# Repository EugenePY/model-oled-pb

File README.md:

# OLED-UTIL

graphic-converter uitls for **ModelOLED**.

## Installation

```zsh
pip install ./ 
```

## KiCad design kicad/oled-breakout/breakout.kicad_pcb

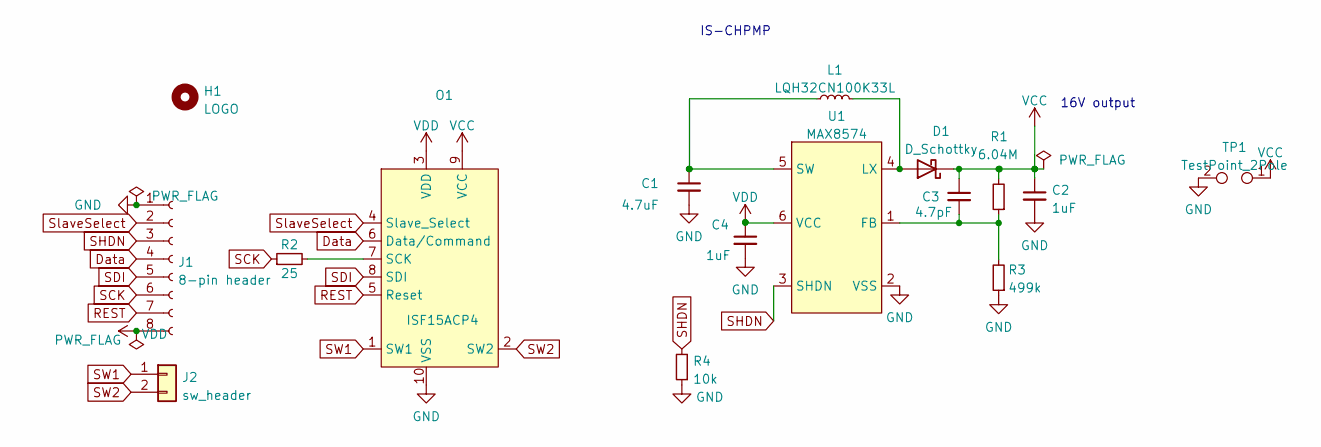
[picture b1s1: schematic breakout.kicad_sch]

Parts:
C1: 4.7uF; C_0603_1608Metric; PART_ID 0603X475M6R3CT
C2, C4: 1uF; C_0603_1608Metric; PART_ID CS1608X7R105K250NRB
C3: 4.7pF; C_0603_1608Metric; PART_ID 0603CG4R7C500NT
D1: D_Schottky; D_SOD-323; PART_ID BAT43WS_R1_00001
H1: LOGO; icon-temp
J1: 8-pin header; PinHeader_1x08_P1.27mm_Vertical
J2: sw_header; PinHeader_1x02_P1.27mm_Vertical
L1: LQH32CN100K33L; L_1210_3225Metric; PART_ID LQH32CN100K33
O1: ISF15ACP4; AT9704-085L; PART_ID ISF15ACP4
R1: 6.04M; R_0805_2012Metric; PART_ID RC0805FR-076M04L
R2: 25; R_0805_2012Metric; PART_ID ARG05BTC0250N
R3: 499k; R_0805_2012Metric; PART_ID ARG05BTC4993
R4: 10k; R_0603_1608Metric; PART_ID RC0603JR-0710KL
TP1: TestPoint_2Pole; TestPoint_2Pads_Pitch2.54mm_Drill0.8mm
U1: MAX8574; SOT-23-6; PART_ID MAX8574EUT+T

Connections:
Data: J1.4, O1.6 (Data/Command)
GND: C1.2, C2.2, C4.2, J1.1, O1.10 (VSS), R3.1, R4.1, TP1.2, U1.2 (VSS)
unnamed: C1.1, L1.1, U1.5 (SW)
unnamed: C3.2, R1.1, R3.2, U1.1 (FB)
unnamed: D1.2 (A), L1.2, U1.4 (LX)
unnamed: O1.7 (SCK), R2.2
REST: J1.7, O1.5 (Reset)
SCK: J1.6, R2.1
SDI: J1.5, O1.8 (SDI)
SHDN: J1.3, R4.2, U1.3 (SHDN)
SW1: J2.1, O1.1 (SW1)
SW2: J2.2, O1.2 (SW2)
SlaveSelect: J1.2, O1.4 (Slave_Select)
VCC: C2.1, C3.1, D1.1 (K), O1.9 (VCC), R1.2, TP1.1
VDD: C4.1, J1.8, O1.3 (VDD), U1.6 (VCC)

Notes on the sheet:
IS-CHPMP
16V output

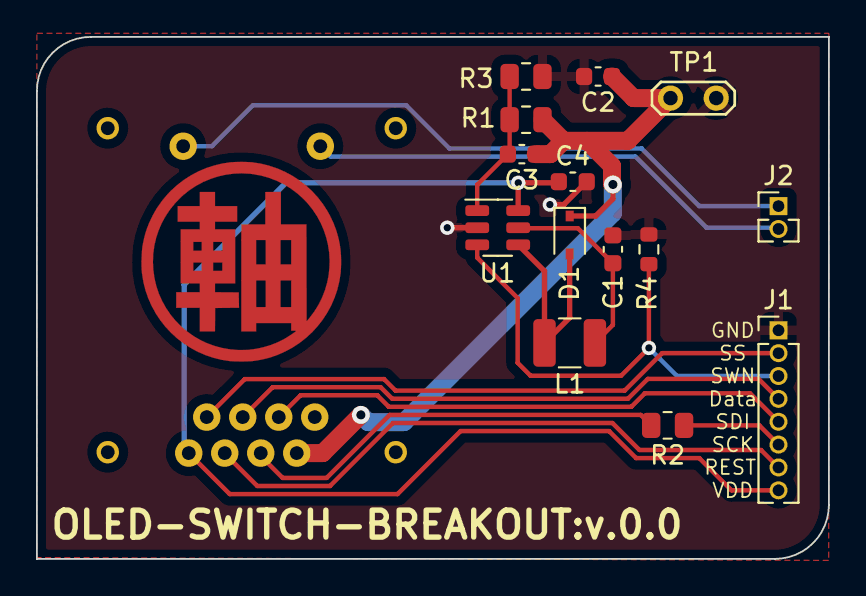
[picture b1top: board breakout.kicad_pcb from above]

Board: 2 copper layers, 44.0 x 29.0 mm, 16 parts (0 on the bottom side), 15 nets.

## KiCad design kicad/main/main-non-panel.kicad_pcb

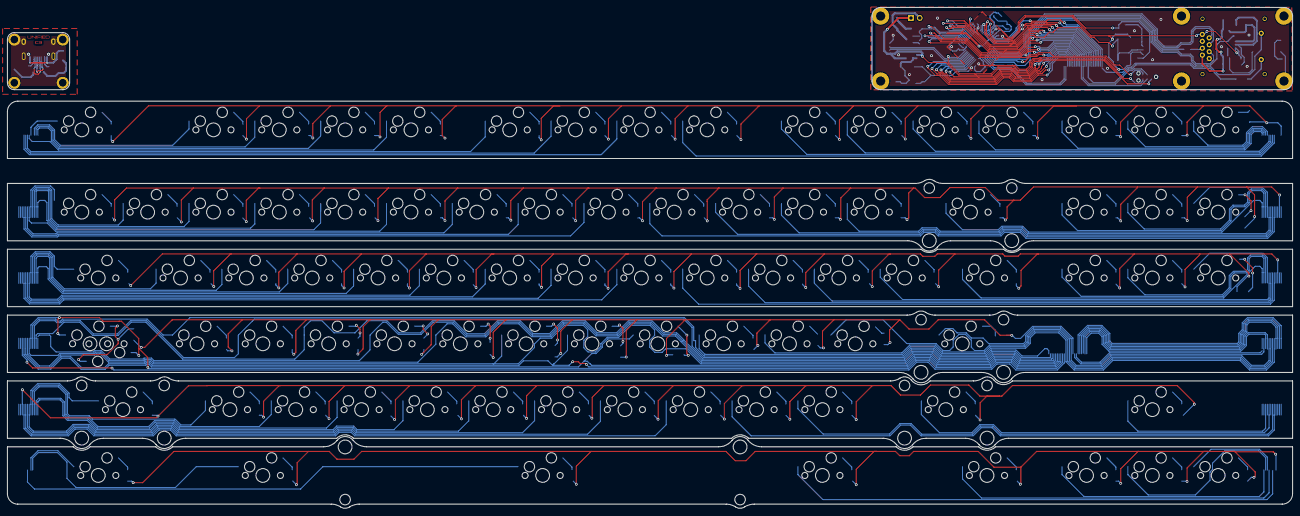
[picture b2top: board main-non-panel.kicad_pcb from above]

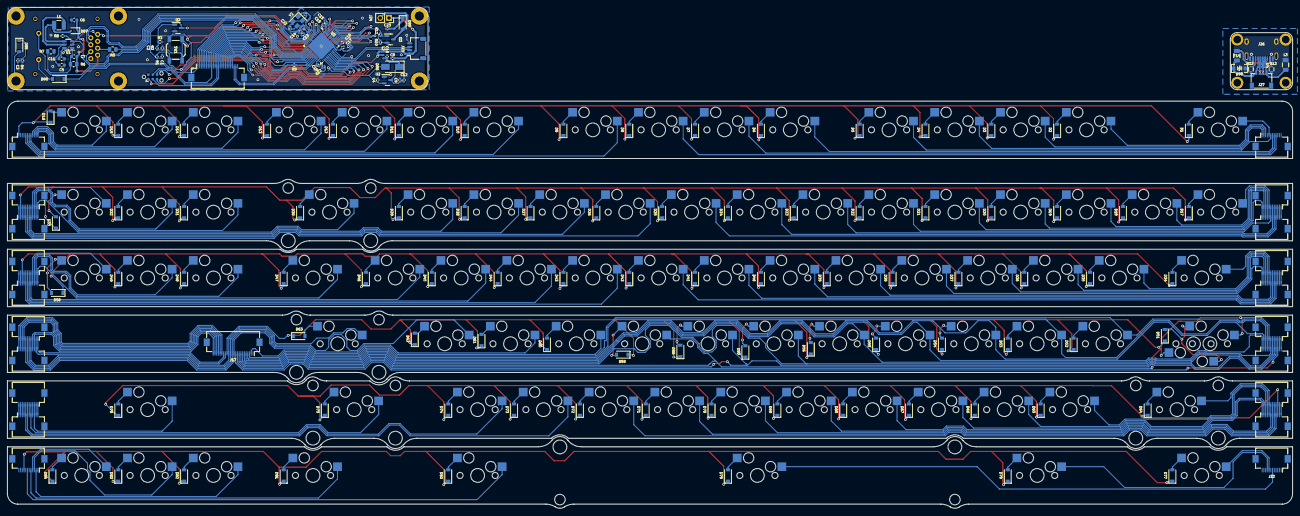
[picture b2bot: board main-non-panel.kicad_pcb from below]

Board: 2 copper layers, 371.9 x 144.9 mm, 263 parts (169 on the bottom side), 144 nets.

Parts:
!1: MX-NoLED; MXOnly-1U-Hotswap
$1: MX-NoLED; MXOnly-1U-Hotswap
%1: MX-NoLED; MXOnly-1U-Hotswap
&1: MX-NoLED; MXOnly-1U-Hotswap
''1: MX-NoLED; MXOnly-1U-Hotswap
(1: MX-NoLED; MXOnly-1U-Hotswap
)1: MX-NoLED; MXOnly-1U-Hotswap
*1: MX-NoLED; MXOnly-1U-Hotswap
+1: MX-NoLED; MXOnly-1U-Hotswap
:1: MX-NoLED; MXOnly-1U-Hotswap
<1: MX-NoLED; MXOnly-1U-Hotswap
>1: MX-NoLED; MXOnly-1U-Hotswap
@1: MX-NoLED; MXOnly-1U-Hotswap
A1: MX-NoLED; MXOnly-1U-Hotswap
B1: MX-NoLED; MXOnly-1U-Hotswap
BS1: MX-NoLED; MXOnly-2U-Hotswap
C1: 470nF; C_0402_1005Metric
C2, C3, C20, C23: 4.7uF; C_0402_1005Metric
C4, C12, C14: 1uF; C_0402_1005Metric
C5: 4.7uF; C_0603_1608Metric
C6, C11: 1uF; C_0603_1608Metric
C7: 4.7pF; C_0603_1608Metric
C8, C13: 10nF; C_0402_1005Metric
C9, C15, C16, C17, C18, C19: 100nF; C_0402_1005Metric
C10: 4.7nF; C_0402_1005Metric
C21, C22: 30pF; C_0402_1005Metric
CAP1: MX-NoLED; MXOnly-1.75U-Hotswap
CAP2: Steped-Cap; MXOnly-1.25U-Hotswap
D1, D2, D3, D4, D5, D6, D7, D8, D9, D10, D11, D12, D13, D14, D15, D16, D17, D18, D19, D20, D21, D22, D23, D24, D25, D26, D27, D28, D29, D30, D31, D32, D33, D34, D35, D36, D37, D38, D39, D40, D41, D42, D43, D44, D45, D46, D47, D48, D49, D50, D51, D52, D53, D54, D55, D56, D57, D58, D59, D60, D61, D62, D63, D64, D65, D66, D67, D68, D69, D70, D71, D72, D73, D74, D75, D76, D77, D78, D79, D80, D81, D82, D83, D84, D85, D88: 1N4148W; D_SOD-123
D86: SS34; D_SMA
D87: D_Schottky; D_SOD-323
D89: freewheeling diode; D_SOD-123
D90: SMF9.0CA; D_SOD-123_Bidirectional
Delete1: MX-NoLED; MXOnly-1U-Hotswap
Down1: MX-NoLED; MXOnly-1U-Hotswap
E1: MX-NoLED; MXOnly-1U-Hotswap
End1: MX-NoLED; MXOnly-1U-Hotswap
Enter1: MX-NoLED; MXOnly-2.25U-Hotswap
Esc1: MX-NoLED; MXOnly-1U-Hotswap
F1, F2, F3, F4, F5, F6, F7, F8, F9, F10, F11, F12, F13: MX-NoLED; MXOnly-1U-Hotswap
F14: ASMD1206-150; Fuse_1206_3216Metric
G1: MX-NoLED; MXOnly-1U-Hotswap
G2: name; Unified-Daughterboard-Name.pretty
G3: logo; Unified-Daughterboard-Logo.pretty
H1: MX-NoLED; MXOnly-1U-Hotswap
H2, H3, H4, H5, H6, H7: M2.5; MountingHole_2.7mm_M2.5_Pad
Home1: MX-NoLED; MXOnly-1U-Hotswap
I1: MX-NoLED; MXOnly-1U-Hotswap
Insert1: MX-NoLED; MXOnly-1U-Hotswap
J1, J3, J5, J7, J9, J11, J13, J15, J19, J21: Conn_01x12_Male; Hirose_FH12-12S-0.5SH_1x12-1MP_P0.50mm_Horizontal
J2, J4, J6, J8, J10, J12, J14, J18, J20, J22: Conn_01x12_Female; Hirose_FH12-12S-0.5SH_1x12-1MP_P0.50mm_Horizontal
J16, J17: switch_board; Hirose_FH12-24S-0.5SH_1x24-1MP_P0.50mm_Horizontal
J23: JST-4 pins; JST_SH_SM04B-SRSS-TB_1x04-1MP_P1.00mm_Horizontal
J24: solenoid; PinSocket_1x02_P2.54mm_Vertical
J25: SWD/JTAG-4pin; Tag-Connect_TC2030-IDC-NL_2x03_P1.27mm_Vertical
J26: TYPE-C-31-M12_13; TYPE-C-31-M-12
J27: JST-4 pins; JST-SR-4
K1: MX-NoLED; MXOnly-1U-Hotswap
L1: LQH32CN100K33L; L_1210_3225Metric
L2: 33R@100MH; L_0402_1005Metric
L3: 60R@100MHz; L_1206_3216Metric
LAlt1: MX-NoLED; MXOnly-1.5U-Hotswap
LCtrl1: MX-NoLED; MXOnly-1.5U-Hotswap
LShift1: MX-NoLED; MXOnly-2.25U-Hotswap
Left1: MX-NoLED; MXOnly-1U-Hotswap
M1: MX-NoLED; MXOnly-1U-Hotswap
MH1, MH2, MH4: Mount-M2; Generic-Mounthole
MH3: mouting-hole; Generic-Mounthole
MX_C1: MX-NoLED; MXOnly-1U-Hotswap
MX_D1: MX-NoLED; MXOnly-1U-Hotswap
MX_J1: MX-NoLED; MXOnly-1U-Hotswap
MX_L1: MX-NoLED; MXOnly-1U-Hotswap
MX_R1: MX-NoLED; MXOnly-1U-Hotswap
MX_U1: MX-NoLED; MXOnly-1U-Hotswap
N1: MX-NoLED; MXOnly-1U-Hotswap
O1: MX-NoLED; MXOnly-1U-Hotswap
O2: ISF15ACP4; AT9704-085L
P1: MX-NoLED; MXOnly-1U-Hotswap
PB1: MX-NoLED; MXOnly-1U-Hotswap
PgDn1: MX-NoLED; MXOnly-1U-Hotswap
PgUp1: MX-NoLED; MXOnly-1U-Hotswap
PrtSc1: MX-NoLED; MXOnly-1U-Hotswap
Q1: MX-NoLED; MXOnly-1U-Hotswap
Q2: 2N7002; SOT-23
Q3: SI2302; SOT-23
R1, R2, R8, R9, R10: 10k; R_0402_1005Metric
R3: 100k; R_0402_1005Metric
R4: 1M; R_0402_1005Metric
R5: 25; R_0805_2012Metric
R6: 6.04M; R_0805_2012Metric
R7: 499k; R_0805_2012Metric
R11: 1k; R_0402_1005Metric
R12, R13: 5.1k; R_0603
RAlt1: MX-NoLED; MXOnly-1.5U-Hotswap
RCtrl1: MX-NoLED; MXOnly-1.5U-Hotswap
RShift1: MX-NoLED; MXOnly-2.75U-Hotswap
Right1: MX-NoLED; MXOnly-1U-Hotswap
S1: MX-NoLED; MXOnly-1U-Hotswap
SL1: MX-NoLED; MXOnly-1U-Hotswap
SW1: SW_Push; SW_SPST_SKQG_WithoutStem
Spc1: MX-NoLED; MXOnly-7U-Hotswap-ReversedStabilizers
T1: MX-NoLED; MXOnly-1U-Hotswap
TAB1: MX-NoLED; MXOnly-1.5U-Hotswap
U1: MAX8574; SOT-23-6
U2: MCP1754S-3302xCB; SOT-23
U3: STM32F103CBUx; QFN-48-1EP_7x7mm_P0.5mm_EP5.6x5.6mm
U4: TPD4E05U06DQAR; USON-10_2.5x1.0mm_P0.5mm
Up1: MX-NoLED; MXOnly-1U-Hotswap
V1: MX-NoLED; MXOnly-1U-Hotswap
W1: MX-NoLED; MXOnly-1U-Hotswap
X1: MX-NoLED; MXOnly-1U-Hotswap
Y1: MX-NoLED; MXOnly-1U-Hotswap
Y2: 8MHz; Crystal_SMD_3225-4Pin_3.2x2.5mm
Z1: MX-NoLED; MXOnly-1U-Hotswap
\1: MX-NoLED; MXOnly-1U-Hotswap
\#1: MX-NoLED; MXOnly-1U-Hotswap
\QM1: MX-NoLED; MXOnly-1U-Hotswap
^1: MX-NoLED; MXOnly-1U-Hotswap
_1: MX-NoLED; MXOnly-1U-Hotswap
{1: MX-NoLED; MXOnly-1U-Hotswap
|1: MX-NoLED; MXOnly-1.5U-Hotswap
}1: MX-NoLED; MXOnly-1U-Hotswap

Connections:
+5V: C9.1, C10.1, C12.1, D86.1 (K), L2.2, U2.3 (VI)
BOOT0: C2.1, R2.2, SW1.1, U3.44 (BOOT0)
BOOT1: R9.1, U3.20 (PB2)
D+: J23.3, U3.33 (PA12)
D-: J23.2, U3.32 (PA11)
DA+: J26.A6 (D+), J26.B6 (D+), J27.3, U4.1 (IO1), U4.4 (D2+), U4.7 (NC), U4.10 (NC)
DA-: J26.A7 (D-), J26.B7 (D-), J27.2, U4.2 (IO2), U4.5 (D2-), U4.6 (NC), U4.9 (NC)
Data: O2.6 (Data/Command), U3.13 (PA3)
GND: C1.2, C3.2, C4.2, C5.2, C6.2, C8.2, C9.2, C10.2, C11.2, C12.2, C13.2, C14.2, C15.2, C16.2, C17.2, C18.2, C19.2, C20.2, C21.2, C22.1, C23.2, J23.4, J25.2, J27.4, L3.1, O2.10 (VSS), Q2.2 (S), Q3.2 (S), R2.1, R3.2, R4.2, R7.1, R8.1, R9.2, R10.1, U1.2 (VSS), U2.1 (GND), U3.8 (VSSA), U3.23 (VSS), U3.35 (VSS), U3.47 (VSS), U3.49 (VSS), Y2.2, Y2.4
GNDPWR: D90.1 (A1), J26.A1 (GND), J26.B1 (GND), J26.S (SHIELD), L3.2, MH2.1, R12.2, R13.2, U4.3 (GND), U4.8 (GND)
NRST: C1.1, Q2.3 (D), R1.1, U3.7 (NRST)
unnamed: !1.2 (ROW), D18.2 (A)
unnamed: $1.2 (ROW), D21.2 (A)
unnamed: %1.2 (ROW), D22.2 (A)
unnamed: &1.2 (ROW), D24.2 (A)
unnamed: ''1.2 (ROW), D62.2 (A)
unnamed: (1.2 (ROW), D26.2 (A)
unnamed: )1.2 (ROW), D27.2 (A)
unnamed: *1.2 (ROW), D25.2 (A)
unnamed: +1.2 (ROW), D29.2 (A)
unnamed: :1.2 (ROW), D61.2 (A)
unnamed: <1.2 (ROW), D72.2 (A)
unnamed: >1.2 (ROW), D73.2 (A)
unnamed: @1.2 (ROW), D19.2 (A)
unnamed: A1.2 (ROW), D52.2 (A)
unnamed: B1.2 (ROW), D69.2 (A)
unnamed: BS1.2 (ROW), D30.2 (A)
unnamed: C2.2, Q2.1 (G), R3.1
unnamed: C3.1, D85.1 (K), R4.1
unnamed: C5.1, L1.1, U1.5 (SW)
unnamed: C7.2, R6.1, R7.2, U1.1 (FB)
unnamed: CAP1.2 (ROW), CAP2.2 (ROW), D51.2 (A)
unnamed: D1.2 (A), Esc1.2 (ROW)
unnamed: D2.2 (A), F1.2 (ROW)
unnamed: D3.2 (A), F2.2 (ROW)
unnamed: D4.2 (A), F3.2 (ROW)
unnamed: D5.2 (A), F4.2 (ROW)
unnamed: D6.2 (A), F5.2 (ROW)
unnamed: D7.2 (A), F6.2 (ROW)
unnamed: D8.2 (A), F7.2 (ROW)
unnamed: D9.2 (A), F8.2 (ROW)
unnamed: D10.2 (A), F9.2 (ROW)
unnamed: D11.2 (A), F10.2 (ROW)
unnamed: D12.2 (A), F11.2 (ROW)
unnamed: D13.2 (A), F12.2 (ROW)
unnamed: D14.2 (A), PrtSc1.2 (ROW)
unnamed: D15.2 (A), SL1.2 (ROW)
unnamed: D16.2 (A), PB1.2 (ROW)
unnamed: D17.2 (A), \1.2 (ROW)
unnamed: D20.2 (A), \#1.2 (ROW)
unnamed: D23.2 (A), ^1.2 (ROW)
unnamed: D28.2 (A), _1.2 (ROW)
unnamed: D31.2 (A), Insert1.2 (ROW)
unnamed: D32.2 (A), Home1.2 (ROW)
unnamed: D33.2 (A), PgUp1.2 (ROW)
unnamed: D34.2 (A), TAB1.2 (ROW)
unnamed: D35.2 (A), Q1.2 (ROW)
unnamed: D36.2 (A), W1.2 (ROW)
unnamed: D37.2 (A), E1.2 (ROW)
unnamed: D38.2 (A), MX_R1.2 (ROW)
unnamed: D39.2 (A), T1.2 (ROW)
unnamed: D40.2 (A), Y1.2 (ROW)
unnamed: D41.2 (A), MX_U1.2 (ROW)
unnamed: D42.2 (A), I1.2 (ROW)
unnamed: D43.2 (A), O1.2 (ROW)
unnamed: D44.2 (A), P1.2 (ROW)
unnamed: D45.2 (A), {1.2 (ROW)
unnamed: D46.2 (A), }1.2 (ROW)
unnamed: D47.2 (A), |1.2 (ROW)
unnamed: D48.2 (A), Delete1.2 (ROW)
unnamed: D49.2 (A), End1.2 (ROW)
unnamed: D50.2 (A), PgDn1.2 (ROW)
unnamed: D53.2 (A), S1.2 (ROW)
unnamed: D54.2 (A), MX_D1.2 (ROW)
unnamed: D55.2 (A), F13.2 (ROW)
unnamed: D56.2 (A), G1.2 (ROW)
unnamed: D57.2 (A), H1.2 (ROW)
unnamed: D58.2 (A), MX_J1.2 (ROW)
unnamed: D59.2 (A), K1.2 (ROW)
unnamed: D60.2 (A), MX_L1.2 (ROW)
unnamed: D63.2 (A), Enter1.2 (ROW)
unnamed: D64.2 (A), LShift1.2 (ROW)
unnamed: D65.2 (A), Z1.2 (ROW)
unnamed: D66.2 (A), X1.2 (ROW)
unnamed: D67.2 (A), MX_C1.2 (ROW)
unnamed: D68.2 (A), V1.2 (ROW)
unnamed: D70.2 (A), N1.2 (ROW)
unnamed: D71.2 (A), M1.2 (ROW)
unnamed: D74.2 (A), \QM1.2 (ROW)
unnamed: D75.2 (A), RShift1.2 (ROW)
unnamed: D76.2 (A), Up1.2 (ROW)
unnamed: D77.2 (A), LCtrl1.2 (ROW)
unnamed: D78.2 (A), LAlt1.2 (ROW)
unnamed: D79.2 (A), Spc1.2 (ROW)
unnamed: D80.2 (A), RAlt1.2 (ROW)
unnamed: D81.2 (A), RCtrl1.2 (ROW)
unnamed: D82.2 (A), Left1.2 (ROW)
unnamed: D83.2 (A), Down1.2 (ROW)
unnamed: D84.2 (A), Right1.2 (ROW)
unnamed: D85.2 (A), H2.1
unnamed: D87.2 (A), L1.2, U1.4 (LX)
unnamed: J26.A5 (CC1), R12.1
unnamed: J26.B5 (CC2), R13.1
unnamed: O2.7 (SCK), R5.2
unnamed: Q3.1 (G), R11.2
OLED_SHDN: R8.2, U1.3 (SHDN), U3.19 (PB1)
R0C0_1: $1.1 (COL), F3.1 (COL), F13.1 (COL), J1.1, J2.12, J5.1, J6.12, J9.1, J10.12, J15.1, J16.20, J17.5, J18.12, J21.1, J22.12, MX_R1.1 (COL), U3.30 (PA9), V1.1 (COL)
R0C0_2: E1.1 (COL), F2.1 (COL), J1.2, J2.11, J5.2, J6.11, J9.2, J10.11, J15.2, J16.21, J17.4, J18.11, J21.2, J22.11, MX_C1.1 (COL), MX_D1.1 (COL), U3.31 (PA10), \#1.1 (COL)
R0C0_3: @1.1 (COL), F1.1 (COL), J1.3, J2.10, J5.3, J6.10, J9.3, J10.10, J15.3, J16.22, J17.3, J18.10, J21.3, J22.10, S1.1 (COL), U3.22 (PB11), W1.1 (COL), X1.1 (COL)
R0C0_4: !1.1 (COL), A1.1 (COL), J1.4, J2.9, J5.4, J6.9, J9.4, J10.9, J15.4, J16.23, J17.2, J18.9, J21.4, J22.9, LAlt1.1 (COL), Q1.1 (COL), U3.21 (PB10), Z1.1 (COL)
R0C0_5: CAP1.1 (COL), CAP2.1 (COL), Esc1.1 (COL), J1.5, J2.8, J5.5, J6.8, J9.5, J10.8, J15.5, J16.15, J17.10, J18.8, J21.5, J22.8, LCtrl1.1 (COL), LShift1.1 (COL), TAB1.1 (COL), U3.18 (PB0), \1.1 (COL)
R0C0_6: %1.1 (COL), B1.1 (COL), F4.1 (COL), G1.1 (COL), J1.6, J2.7, J5.6, J6.7, J9.6, J10.7, J15.6, J16.19, J17.6, J18.7, J21.6, J22.7, T1.1 (COL), U3.29 (PA8)
R0C0_7: F5.1 (COL), H1.1 (COL), J1.7, J2.6, J5.7, J6.6, J9.7, J10.6, J15.7, J16.18, J17.7, J18.6, J21.7, J22.6, N1.1 (COL), Spc1.1 (COL), U3.28 (PB15), Y1.1 (COL), ^1.1 (COL)
R0C0_8: &1.1 (COL), F6.1 (COL), J1.8, J2.5, J5.8, J6.5, J9.8, J10.5, J15.8, J16.16, J17.9, J18.5, J21.8, J22.5, M1.1 (COL), MX_J1.1 (COL), MX_U1.1 (COL), U3.26 (PB13)
R0C0_9: *1.1 (COL), <1.1 (COL), F7.1 (COL), I1.1 (COL), J1.9, J2.4, J5.9, J6.4, J9.9, J10.4, J15.9, J16.17, J17.8, J18.4, J21.9, J22.4, K1.1 (COL), U3.27 (PB14)
R0C0_10: D64.1 (K), D65.1 (K), D66.1 (K), D67.1 (K), D68.1 (K), D69.1 (K), D70.1 (K), D71.1 (K), D72.1 (K), D73.1 (K), D74.1 (K), D75.1 (K), D76.1 (K), J1.10, J2.3, J5.10, J6.3, J9.10, J10.3, J15.10, J16.14, J17.11, J18.3, J21.10, J22.3, U3.16 (PA6)
R0C0_11: J1.11, J2.2, J5.11, J6.2, J9.11, J10.2, J15.11, J18.2, J21.11, J22.2
R0C0_12: J1.12, J2.1, J5.12, J6.1, J9.12, J10.1, J15.12, J18.1, J21.12, J22.1
R0C1_1: D1.1 (K), D2.1 (K), D3.1 (K), D4.1 (K), D5.1 (K), D6.1 (K), D7.1 (K), D8.1 (K), D9.1 (K), D10.1 (K), D11.1 (K), D12.1 (K), D13.1 (K), D14.1 (K), D15.1 (K), D16.1 (K), J3.1, J4.12, J7.1, J8.12, J11.1, J12.12, J13.1, J14.12, J16.6, J17.19, J19.1, J20.12, U3.2 (PC13)
R0C1_2: D17.1 (K), D18.1 (K), D19.1 (K), D20.1 (K), D21.1 (K), D22.1 (K), D23.1 (K), D24.1 (K), D25.1 (K), D26.1 (K), D27.1 (K), D28.1 (K), D29.1 (K), D30.1 (K), D31.1 (K), D32.1 (K), D33.1 (K), J3.2, J4.11, J7.2, J8.11, J11.2, J12.11, J13.2, J14.11, J16.5, J17.20, J19.2, J20.11, U3.3 (PC14)
R0C1_3: D34.1 (K), D35.1 (K), D36.1 (K), D37.1 (K), D38.1 (K), D39.1 (K), D40.1 (K), D41.1 (K), D42.1 (K), D43.1 (K), D44.1 (K), D45.1 (K), D46.1 (K), D47.1 (K), D48.1 (K), D49.1 (K), D50.1 (K), J3.3, J4.10, J7.3, J8.10, J11.3, J12.10, J13.3, J14.10, J16.4, J17.21, J19.3, J20.10, U3.4 (PC15)
R0C1_4: D77.1 (K), D78.1 (K), D79.1 (K), D80.1 (K), D81.1 (K), D82.1 (K), D83.1 (K), D84.1 (K), J3.4, J4.9, J7.4, J8.9, J11.4, J12.9, J13.4, J14.9, J16.3, J17.22, J19.4, J20.9, U3.12 (PA2)
R0C1_5: (1.1 (COL), >1.1 (COL), F8.1 (COL), J3.5, J4.8, J7.5, J8.8, J11.5, J12.8, J13.5, J14.8, J16.13, J17.12, J19.5, J20.8, J25.3, MX_L1.1 (COL), O1.1 (COL), U3.38 (PA15)
R0C1_6: )1.1 (COL), :1.1 (COL), F9.1 (COL), J3.6, J4.7, J7.6, J8.7, J11.6, J12.7, J13.6, J14.7, J16.12, J17.13, J19.6, J20.7, J25.4, P1.1 (COL), RAlt1.1 (COL), U3.39 (PB3), \QM1.1 (COL)
R0C1_7: ''1.1 (COL), F10.1 (COL), J3.7, J4.6, J7.7, J8.6, J11.7, J12.6, J13.7, J14.6, J16.11, J17.14, J19.7, J20.6, U3.41 (PB5), _1.1 (COL), {1.1 (COL)
R0C1_8: +1.1 (COL), Enter1.1 (COL), F11.1 (COL), J3.8, J4.5, J7.8, J8.5, J11.8, J12.5, J13.8, J14.5, J16.10, J17.15, J19.8, J20.5, RCtrl1.1 (COL), RShift1.1 (COL), U3.42 (PB6), }1.1 (COL)
R0C1_9: J3.9, J4.4, J7.9, J8.4, J11.9, J12.4, J13.9, J14.4, J16.2, J17.23, J19.9, J20.4, PB1.1 (COL), PgDn1.1 (COL), PgUp1.1 (COL), Right1.1 (COL), U3.11 (PA1)
R0C1_10: Down1.1 (COL), End1.1 (COL), Home1.1 (COL), J3.10, J4.3, J7.10, J8.3, J11.10, J12.3, J13.10, J14.3, J16.1, J17.24, J19.10, J20.3, O2.1 (SW1), SL1.1 (COL), U3.10 (PA0), Up1.1 (COL)
R0C1_11: Delete1.1 (COL), Insert1.1 (COL), J3.11, J4.2, J7.11, J8.2, J11.11, J12.2, J13.11, J14.2, J16.8, J17.17, J19.11, J20.2, Left1.1 (COL), PrtSc1.1 (COL), U3.45 (PB8)
R0C1_12: BS1.1 (COL), F12.1 (COL), J3.12, J4.1, J7.12, J8.1, J11.12, J12.1, J13.12, J14.1, J16.7, J17.18, J19.12, J20.1, U3.46 (PB9), |1.1 (COL)
RCC_OSC_IN: C21.1, U3.5 (PD0), Y2.1
RCC_OSC_OUT: C22.2, U3.6 (PD1), Y2.3
SCK: R5.1, U3.15 (PA5)
SDI: O2.8 (SDI), U3.17 (PA7)
SPI1_NSS: O2.4 (Slave_Select), U3.14 (PA4)
SW2: D88.2 (A), O2.2 (SW2)
SYS_SWCLK: J25.6, U3.37 (PA14)
SYS_SWDIO: J25.5, U3.34 (PA13)
Solenoid_Driver: R10.2, R11.1, U3.40 (PB4)
Solenoid_Neg: D89.2 (A), J24.2, Q3.3 (D)
Solenoid_Pos: C8.1, C23.1, D89.1 (K), F14.1, J23.1, J24.1, J25.1, J26.A4 (VBUS), J26.B4 (VBUS), L2.1
VCC: C6.1, C7.1, D87.1 (K), D90.2 (A2), F14.2, J27.1, O2.9 (VCC), R6.2
VDD: C4.1, C11.1, C13.1, C14.1, C15.1, C16.1, C17.1, C18.1, C19.1, C20.1, D86.2 (A), O2.3 (VDD), R1.2, SW1.2, U1.6 (VCC), U2.2 (VO), U3.1 (VBAT), U3.9 (VDDA), U3.24 (VDD), U3.36 (VDD), U3.48 (VDD)
row3: D51.1 (K), D52.1 (K), D53.1 (K), D54.1 (K), D55.1 (K), D56.1 (K), D57.1 (K), D58.1 (K), D59.1 (K), D60.1 (K), D61.1 (K), D62.1 (K), D63.1 (K), D88.1 (K), J16.9, J17.16, U3.43 (PB7)

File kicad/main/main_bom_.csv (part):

Component,Description,Part,References,Value,Footprint,Quantity Per PCB,Datasheet,Part#,PART_ID,suggestion,Manufactor,Package,LCSC Part No,Manufacturer,Manufacturer Part No
1,,MX-NoLED,!1 $1 %1 &1 ''1 (1 )1 *1 +1 :1 <1 >1 @1 A1 B1 Delete1 Down1 E1 End1 Esc1 F1 F2 F3 F4 F5 F6 F7 F8 F9 F10 F11 F12 F13 G1 H1 Home1 I1 Insert1 K1 Left1 M1 MX_C1 MX_D1 MX_J1 MX_L1 MX_R1 MX_U1 N1 O1 P1 PB1 PgDn1 PgUp1 PrtSc1 Q1 Right1 S1 SL1 T1 Up1 V1 W1 X1 Y1 Z1 \1 \#1 \QM1 ^1 _1 {1 }1,MX-NoLED,MXOnly-1U-Hotswap,72,,Kailh Hotswap Socket,,,,,,,
2,,MX-NoLED,BS1,MX-NoLED,MXOnly-2U-Hotswap,1,,Kailh Hotswap Socket,,,,,,,
3,"Unpolarized capacitor, small symbol",C_Small,C7,4.7pF,C_0603_1608Metric,1,~,0603CG4R7C500NT,0603CG4R7C500NT,"4.7pF, SM0805, 50V, COG",,,,,
4,"Unpolarized capacitor, small symbol",C_Small,C21 C22,30pF,C_0402_1005Metric,2,~,GCM1555C1H300JA16D,,,Murata Electronics,,,,
5,"Unpolarized capacitor, small symbol",C_Small,C10,4.7nF,C_0402_1005Metric,1,~,,,,Taiyo Yuden,,,,
6,"Unpolarized capacitor, small symbol",C_Small,C8 C13,10nF,C_0402_1005Metric,2,~,,,,CCTC Vishay Intertech,,,,
7,"Unpolarized capacitor, small symbol",C_Small,C9 C15 C16 C17 C18 C19 C24,100nF,C_0402_1005Metric,7,~,,,,Vishay Intertech,,,,
8,"Unpolarized capacitor, small symbol",C_Small,C1,470nF,C_0402_1005Metric,1,~,,,,Taiyo Yuden,,,,
9,"Unpolarized capacitor, small symbol",C_Small,C6 C11,1uF,C_0603_1608Metric,2,~,CS1608X7R105K250NRB,CS1608X7R105K250NRB,"1uF, SM0805, 25V, X7R 1uF, SM0805, 16V, X7R",,,,,
10,"Unpolarized capacitor, small symbol",C_Small,C4 C12 C14,1uF,C_0402_1005Metric,3,~,EMK105BJ105KV-F,,,Taiyo Yuden,C0402,,,
11,"Unpolarized capacitor, small symbol",C_Small,C2 C3 C20 C23,4.7uF,C_0402_1005Metric,4,~,,,,Taiyo Yuden,,,,
12,"Unpolarized capacitor, small symbol",C_Small,C5,4.7uF,C_0603_1608Metric,1,~,0603X475M6R3CT,0603X475M6R3CT,"4.7uF, SM0805, 6.3V, X5R",,,,,
13,,MX-NoLED,CAP1,MX-NoLED,MXOnly-1.75U-Hotswap,1,,Kailh Hotswap Socket,,,,,,,
14,,MX-NoLED,CAP2,Steped-Cap,MXOnly-1.25U-Hotswap,1,,Kailh Hotswap Socket,,,,,,,
15,"Diode, small symbol",D_Small,D1 D2 D3 D4 D5 D6 D7 D8 D9 D10 D11 D12 D13 D14 D15 D16 D17 D18 D19 D20 D21 D22 D23 D24 D25 D26 D27 D28 D29 D30 D31 D32 D33 D34 D35 D36 D37 D38 D39 D40 D41 D42 D43 D44 D45 D46 D47 D48 D49 D50 D51 D52 D53 D54 D55 D56 D57 D58 D59 D60 D61 D62 D63 D64 D65 D66 D67 D68 D69 D70 D71 D72 D73 D74 D75 D76 D77 D78 D79 D80 D81 D82 D83 D84 D85 D88,1N4148W,D_SOD-123,86,~,1N4148W,,,,,,,
16,Schottky diode,D_Schottky,D87,D_Schottky,D_SOD-323,1,~,BAT43WS_R1_00001,BAT43WS_R1_00001,"DIODE, SCHOTTKY, SOD-123, 0.200A, 30V",,,,,
17,Bidirectional transient-voltage-suppression diode,D_TVS,D90,SMF9.0CA,D_SOD-123_Bidirectional,1,~,SMF9.0CA,,,,SOD-123F-B,C123799,Microdiode Electronics,SMF9.0CA
18,Schottky diode,D_Schottky,D86,SS34,D_SMA,1,~,SS34,,,MDD(Microdiode Electronics),,,,
19,"Diode, small symbol",D_Small,D89,freewheeling diode,D_SOD-123,1,~,1N4148W,,,,,,,
20,,MX-NoLED,Enter1 LShift1,MX-NoLED,MXOnly-2.25U-Hotswap,2,,Kailh Hotswap Socket,,,,,,,
21,"Resettable fuse, polymeric positive temperature coefficient",Polyfuse,F14,ASMD1206-150,Fuse_1206_3216Metric,1,~,ASMD1206-150,,,,F1206,C135342,Shenzhen JDT Fuse,ASMD1206-150
22,"Generic connector, single row, 01x12, script generated (kicad-library-utils/schlib/autogen/connector/)",Conn_01x12_Female,J2 J4 J6 J8 J10 J12 J14 J18 J20 J22,Conn_01x12_Female,Hirose_FH12-12S-0.5SH_1x12-1MP_P0.50mm_Horizontal,10,~,FH12-12S-0.5SH,,ribbon=JUSHUO JS05A-12P-030-3-4,,,,,
23,"Generic connector, single row, 01x12, script generated (kicad-library-utils/schlib/autogen/connector/)",Conn_01x12_Male,J1 J3 J5 J7 J9 J11 J13 J15 J19 J21,Conn_01x12_Male,Hirose_FH12-12S-0.5SH_1x12-1MP_P0.50mm_Horizontal,10,~,FH12-12S-0.5SH,,ribbon=JUSHUO JS05A-24P-250-4-8,,,,,
24,"Generic connector, single row, 01x04, script generated (kicad-library-utils/schlib/autogen/connector/)",Conn_01x04_Female,J23,JST-4 pins,JST_SH_SM04B-SRSS-TB_1x04-1MP_P1.00mm_Horizontal,1,~,X1002WRS-04E-LPSWHF,,,XKB Connectivity,,,XKB Connectivity,
25,"Generic connector, single row, 01x04, script generated (kicad-library-utils/schlib/autogen/connector/)",Conn_01x04,J27,JST-4 pins,JST-SR-4,1,~,X1002WRS-04E-LPSWHF,,,XKB Connectivity,,,XKB Connectivity,SM04B-SRSS-TB(LF)(SN)
26,"Generic connector, single row, 01x06, script generated (kicad-library-utils/schlib/autogen/connector/)",Conn_01x06,J25,SWD/JTAG-4pin,Tag-Connect_TC2030-IDC-NL_2x03_P1.27mm_Vertical,1,~,,,,,,,,
27,,TYPE-C-31-M12_13,J26,TYPE-C-31-M12_13,TYPE-C-31-M-12,1,,TYPE-C-31-M-12,,,,,C165948,Korean Hroparts,TYPE-C-31-M-12
28,"Generic connector, single row, 01x02, script generated (kicad-library-utils/schlib/autogen/connector/)",Conn_01x02,J24,solenoid,PinSocket_1x02_P2.54mm_Vertical,1,~,ROB-11015,,,,,,,
29,"Generic connector, single row, 01x24, script generated (kicad-library-utils/schlib/autogen/connector/)",Conn_01x24_Male,J16,switch_board,Hirose_FH12-24S-0.5SH_1x24-1MP_P0.50mm_Horizontal,1,~,FH12-24S-0.5SH,,,,,,,
30,"Generic connector, single row, 01x24, script generated (kicad-library-utils/schlib/autogen/connector/)",Conn_01x24_Female,J17,switch_board,Hirose_FH12-24S-0.5SH_1x24-1MP_P0.50mm_Horizontal,1,~,FH12-24S-0.5SH,,,,,,,
31,"Inductor, small symbol",L_Small,L2,33R@100MH,L_0402_1005Metric,1,~,CBG100505U330T,,,FH(Guangdong Fenghua Advanced Tech),,,,
32,,L_Core_Ferrite-Device,L3,60R@100MHz,L_1206_3216Metric,1,,MLB3216-600P4A(f),,,,L1206,C33600,MELED Industrial,MLB3216-600P4A(f)
33,"Inductor, small symbol",L_Small,L1,LQH32CN100K33L,L_1210_3225Metric,1,~,LQH32CN100K33,LQH32CN100K33,450mA 10uH 390mΩ 1210 Power Inductors ROHS,,,,,
34,,MX-NoLED,LAlt1 LCtrl1 RAlt1 RCtrl1 TAB1 |1,MX-NoLED,MXOnly-1.5U-Hotswap,6,,Kailh Hotswap Socket,,,,,,,
35,,ISF15ACP4,O2,ISF15ACP4,AT9704-085L,1,https://www.nkkswitches.com/wp-content/uploads/2016/03/Appli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,ISF15ACP4,ISF15ACP4,,,,,,
36,"0.115A Id, 60V Vds, N-Channel MOSFET, SOT-23",2N7002,Q2,2N7002,SOT-23,1,https://www.fairchildsemi.com/datasheets/2N/2N7002.pdf,2N7002,,,,,,,
37,"N-MOSFET transistor, gate/source/drain",Q_NMOS_GSD,Q3,SI2302,SOT-23,1,https://datasheet.lcsc.com/lcsc/2109011130_YONGYUTAI-SI2302_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,SI2302,,,,,,,
38,"Resistor, small symbol",R_Small,R5,25,R_0805_2012Metric,1,~,ARG05BTC0250N,ARG05BTC0250N,,,,,,
39,"Resistor, small symbol",R_Small,R11,1k,R_0402_1005Metric,1,~,,,,,,,,
40,"Resistor, small symbol",R_Small,R12 R13,5.1k,R_0603,2,~,RC0603FR-075K1L,,,,R0603,,,
41,"Resistor, small symbol",R_Small,R1 R2 R8 R10,10k,R_0402_1005Metric,4,~,,RC0603JR-0710KL,,TyoHM,,,,
42,"Resistor, small symbol",R_Small,R3,100k,R_0402_1005Metric,1,~,,,,TyoHM,,,,
43,"Resistor, small symbol",R_Small,R7,499k,R_0805_2012Metric,1,~,ARG05BTC4993,ARG05BTC4993,"RESISTOR, 499K, SM0805, 1/8W, 1%",,,,,
44,"Resistor, small symbol",R_Small,R4,1M,R_0402_1005Metric,1,~,,,,,,,,
45,"Resistor, small symbol",R_Small,R6,6.04M,R_0805_2012Metric,1,~,RC0805FR-076M04L,RC0805FR-076M04L,"RESISTOR, 6.04M, SM0805, 1/8W, 1%",,,,,
46,,MX-NoLED,RShift1,MX-NoLED,MXOnly-2.75U-Hotswap,1,,Kailh Hotswap Socket,,,,,,,
47,"Push button switch, generic, two pins",SW_Push,SW1,SW_Push,SW_SPST_SKQG_WithoutStem,1,~,SKQGABE010,,,ALPSALPINE,,,,
48,,MX-NoLED,Spc1,MX-NoLED,MXOnly-7U-Hotswap-ReversedStabilizers,1,,Kailh Hotswap Socket,,,,,,,
49,,MAX8574,U1,MAX8574,SOT-23-6,1,https://pdf1.alldatasheet.com/datasheet-pdf/view/90627/MAXIM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,MAX8574,MAX8574EUT+T,"C, SOT-23-6, LCD STEP-UP DC-DC CONVERTER, 500mA, 2.7V TO 5.5V",,,,,
50,"Fixed 150mA Low Dropout Voltage Regulator, Positive, 3.3V output, SOT-23",MCP1754S-3302xCB,U2,MCP1754S-3302xCB,SOT-23,1,http://ww1.microchip.com/downloads/en/DeviceDoc/20002276C.pdf,MCP1754ST-3302E/CB,,,Microchip Technology,,,,
51,"ARM Cortex-M0 MCU, 128KB flash, 16KB RAM, 48MHz, 2-3.6V, 37 GPIO, LQFP-48",STM32F072CBTx,U3,STM32F072CBTx,LQFP-48_7x7mm_P0.5mm,1,http://www.st.com/st-web-ui/static/active/en/resource/techni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,,,,,,,,
52,,TPD4E05U06DQAR,U4,TPD4E05U06DQAR,USON-10_2.5x1.0mm_P0.5mm,1,,TPD4E05U06DQAR,,,,uSON-10,C138714,Texas Instruments,TPD4E05U06DQAR
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
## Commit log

2023-03-29 init commit for pub
2023-03-29 remove files
2023-03-29 add README.md
2023-03-29 remove .ccls-cache
2023-04-01 adding index
2023-04-02 update index.md for general features.
2023-04-02 init for keymake
2023-04-02 typo fixed
2023-09-24 done oled-utils
2023-09-24 cleanup
2023-09-24 remove kicad
2023-09-24 Deployed 4e3a4c3 with MkDocs version: 1.5.3
2023-12-05 modify the option name
2023-12-05 Deployed b890083 with MkDocs version: 1.5.3
2023-12-05 update docs
